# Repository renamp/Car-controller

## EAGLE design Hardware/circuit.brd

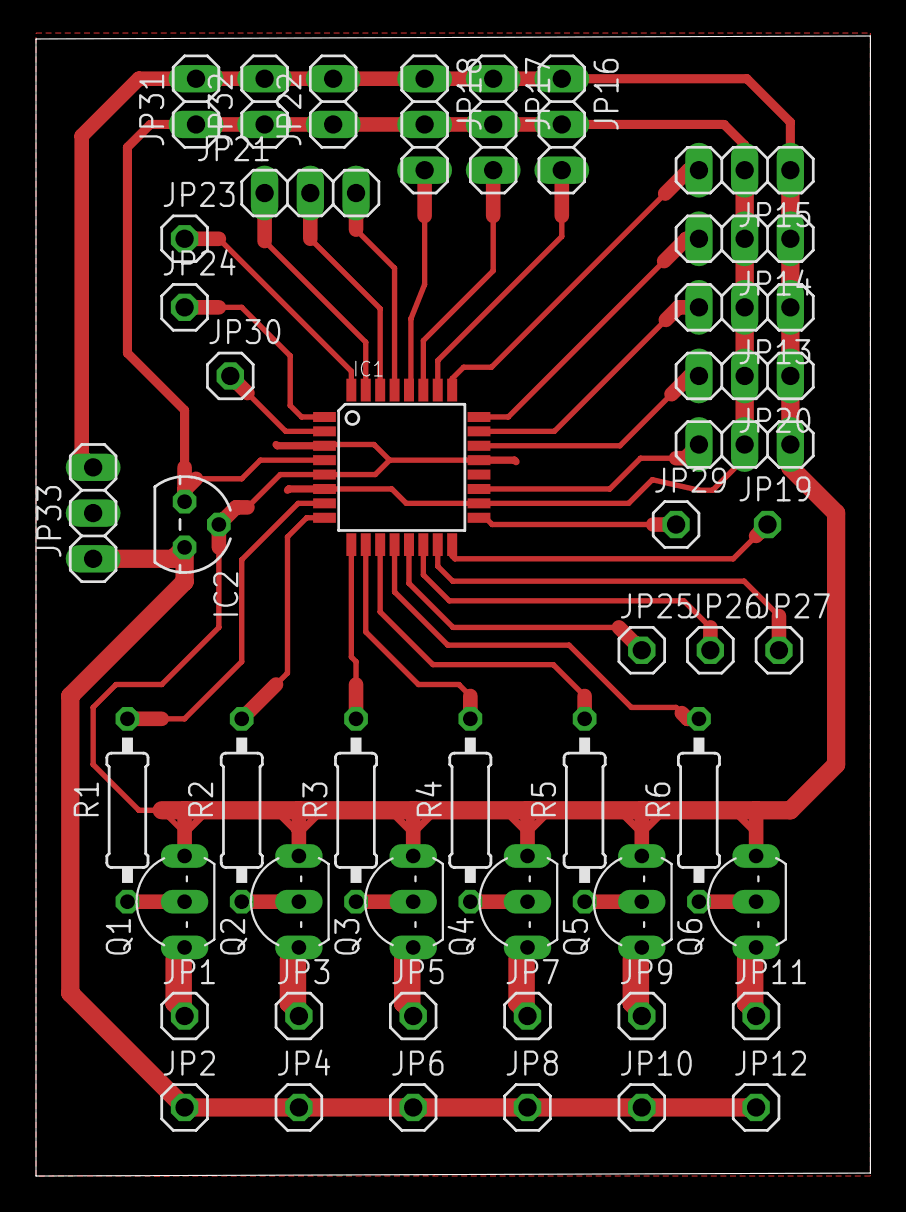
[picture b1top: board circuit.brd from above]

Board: 2 copper layers, 46.4 x 63.3 mm, 47 parts (1 on the bottom side), 40 nets.

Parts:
IC1: MEGA8-AI; TQFP32-08
IC2: 78L05Z; TO92
JP1, JP2, JP3, JP4, JP5, JP6, JP7, JP8, JP9, JP10, JP11, JP12, JP23, JP24, JP25, JP26, JP27, JP28, JP29, JP30: 1X01
JP13, JP14, JP15, JP16, JP17, JP18, JP19, JP20, JP21, JP33: 1X03
JP22, JP31, JP32: 1X02
Q1, Q2, Q3, Q4, Q5, Q6: BC548; TO92-EBC
R1, R2, R3, R4, R5, R6: 10k; 0207/10

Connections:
12V: IC2.3, JP2.1, JP4.1, JP6.1, JP8.1, JP10.1, JP12.1, JP33.1
AIN0: IC1.23, JP13.3
AIN1: IC1.24, JP14.3
AIN2: IC1.25, JP15.3
AIN3: IC1.26, JP16.3
AIN4: IC1.27, JP17.3
AIN5: IC1.28, JP18.3
AIN6: IC1.19, JP19.3
AIN7: IC1.22, JP20.3
DO1: IC1.7, R1.1
DO2: IC1.8, R2.1
DO3: IC1.9, R3.1
DO4: IC1.10, R4.1
DO5: IC1.11, R5.1
DO6: IC1.12, R6.1
GND: IC1.3, IC1.5, IC1.21, IC2.2, JP13.1, JP14.1, JP15.1, JP16.1, JP17.1, JP18.1, JP19.1, JP20.1, JP22.2, JP31.2, JP32.2, JP33.3, Q1.E, Q2.E, Q3.E, Q4.E, Q5.E, Q6.E
MISO: IC1.16, JP28.1
MOSI: IC1.15, JP27.1
MOTOR_L: IC1.1, JP24.1
MOTOR_R: IC1.32, JP23.1
unnamed: Q1.B, R1.2
unnamed: Q2.B, R2.2
unnamed: Q3.B, R3.2
unnamed: Q4.B, R4.2
unnamed: Q5.B, R5.2
unnamed: Q6.B, R6.2
OUT1: JP1.1, Q1.C
OUT2: JP3.1, Q2.C
OUT3: JP5.1, Q3.C
OUT4: JP7.1, Q4.C
OUT5: JP9.1, Q5.C
OUT6: JP11.1, Q6.C
PB1: IC1.13, JP25.1
PB2: IC1.14, JP26.1
PD4: IC1.2, JP30.1
RST: IC1.29, JP21.3
RXD: IC1.30, JP21.2
SCK: IC1.17, JP29.1
TXD: IC1.31, JP21.1
VCC: IC1.4, IC1.6, IC1.18, IC2.1, JP13.2, JP14.2, JP15.2, JP16.2, JP17.2, JP18.2, JP19.2, JP20.2, JP22.1, JP31.1, JP32.1

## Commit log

2021-11-25 Upload project files
2021-11-27 Created .gitignore
2021-11-28 Deleted gcode and edit .gitignore
